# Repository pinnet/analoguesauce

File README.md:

#Analogue Sauce.

Analogue Sauce is initially an operating system targeted at the Raspberry Pi Zero. providing a Quiet Boot environment aimed at the analogue video out capabilities of the device, this coupled with a web based configuration to allow you to create your own subsystem of teletext pages to be added to video playback of SD (standard definition) content on the 'TV' output of the Raspberry Pi Zero. This source can be modulated for RF transmission providing a signal for post modern equipment for test or display.

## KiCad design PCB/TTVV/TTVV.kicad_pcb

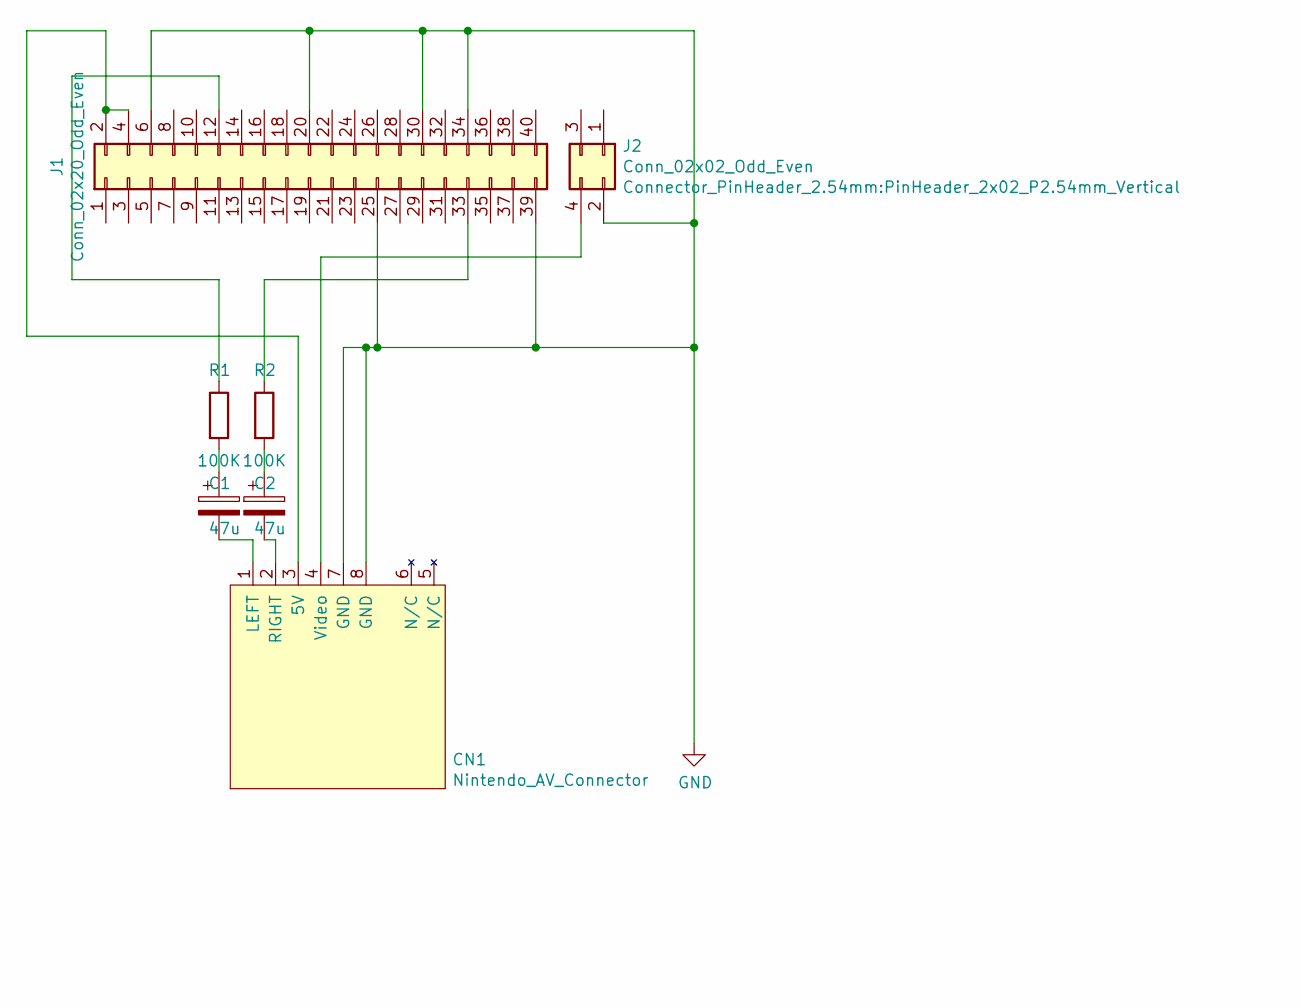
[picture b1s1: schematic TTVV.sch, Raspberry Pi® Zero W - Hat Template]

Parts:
C1, C2: 47u; C_1210_3225Metric_Pad1.42x2.65mm_HandSolder
CN1: Nintendo_AV_Connector; Nintendo_Connector
J1: Conn_02x20_Odd_Even; Nintendo_Connector
J2: Conn_02x02_Odd_Even; PinHeader_2x02_P2.54mm_Vertical
R1, R2: 100K; R_1206_3216Metric_Pad1.42x1.75mm_HandSolder

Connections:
GND: CN1.7 (GND), CN1.8 (GND), J1.6, J1.20, J1.25, J1.30, J1.34, J1.39, J2.2
unnamed: C1.1, R1.2
unnamed: C1.2, CN1.1 (LEFT)
unnamed: C2.1, R2.2
unnamed: C2.2, CN1.2 (RIGHT)
unnamed: CN1.3 (5V), J1.2, J1.4
unnamed: CN1.4 (Video), J2.4
unnamed: J1.12, R1.1
unnamed: J1.33, R2.1

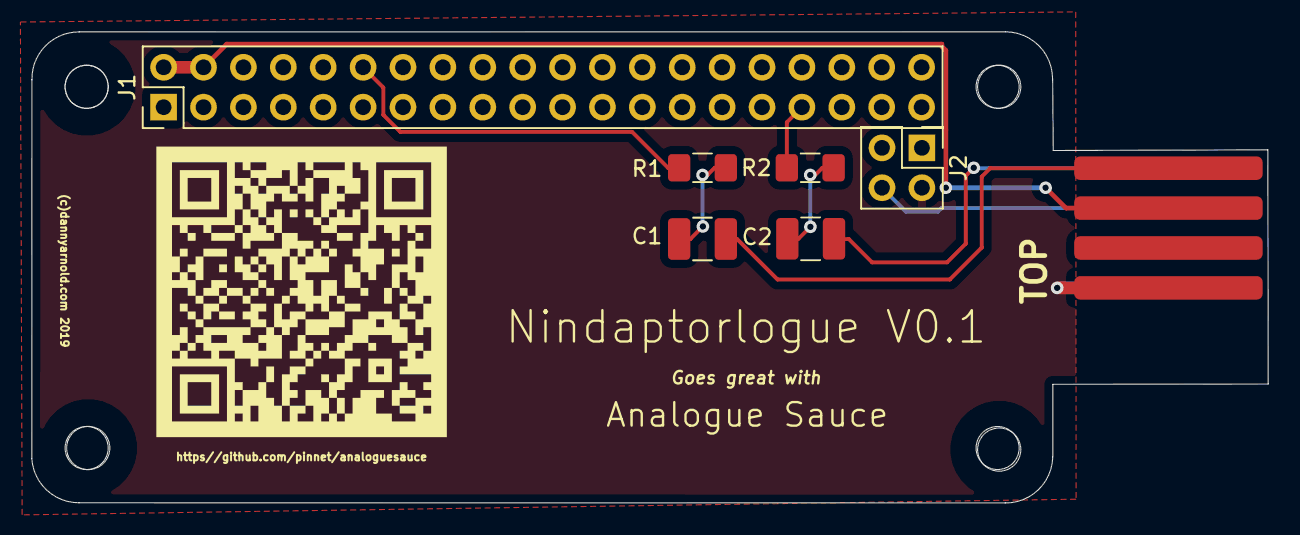
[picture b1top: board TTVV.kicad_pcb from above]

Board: 2 copper layers, 78.7 x 30.0 mm, 8 parts (0 on the bottom side), 9 nets.

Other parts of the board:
https//github.com/pinnet/analoguesauce: QR

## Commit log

2019-12-01 teletext pages commit
2019-12-20 Update one post launch early build ** UNTESTED **
2020-03-17 commit for facebook

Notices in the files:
PCB/TTVV/TTVV.kicad_pcb:
License: MIT - Copyright 2018 StudioPieters®
